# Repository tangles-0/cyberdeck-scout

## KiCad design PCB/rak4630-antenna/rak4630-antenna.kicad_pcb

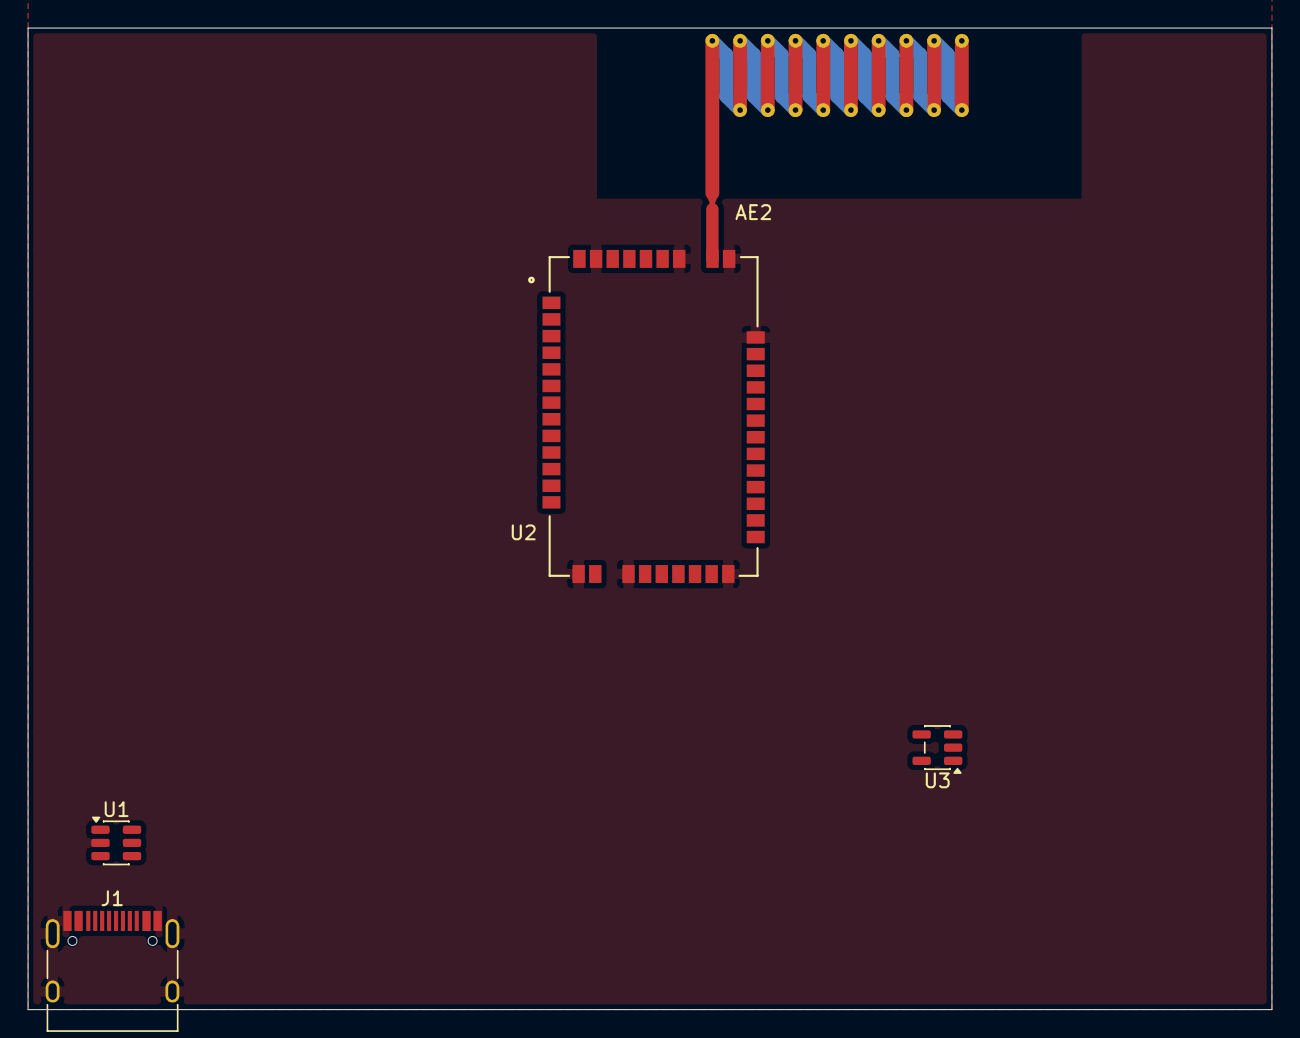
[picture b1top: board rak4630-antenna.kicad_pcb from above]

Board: 2 copper layers, 89.8 x 70.8 mm, 5 parts (0 on the bottom side), 7 nets.

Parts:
AE2: Antenna; Texas_SWRA416_868MHz_915MHz
J1: USB_C_Receptacle_USB2.0_16P; USB_C_Receptacle_HRO_TYPE-C-31-M-12
U1: USBLC6-2SC6; SOT-23-6
U2: RAK4630
U3: AP2112K-3.3; SOT-23-5

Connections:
+VBUS: J1.A4 (VBUS), J1.A9 (VBUS), J1.B4 (VBUS), J1.B9 (VBUS), U1.5 (VBUS), U2.1 (VBUS)
/USBD_N: U1.6 (I/O1), U2.2 (USB-)
/USBD_P: U1.4 (I/O2), U2.3 (USB+)
GND: J1.A1 (GND), J1.A12 (GND), J1.B1 (GND), J1.B12 (GND), J1.S1 (SHIELD), U1.2 (GND), U2.14 (GND1), U2.16 (GND2), U2.22 (GND3), U2.35 (GND4), U2.36 (GND5), U2.38 (GND6), U2.43 (VDD_NRF)
unnamed: AE2.1 (A), U2.37 (RF_LORA)
unnamed: J1.A6 (D+), J1.B6 (D+), U1.3 (I/O2)
unnamed: J1.A7 (D-), J1.B7 (D-), U1.1 (I/O1)

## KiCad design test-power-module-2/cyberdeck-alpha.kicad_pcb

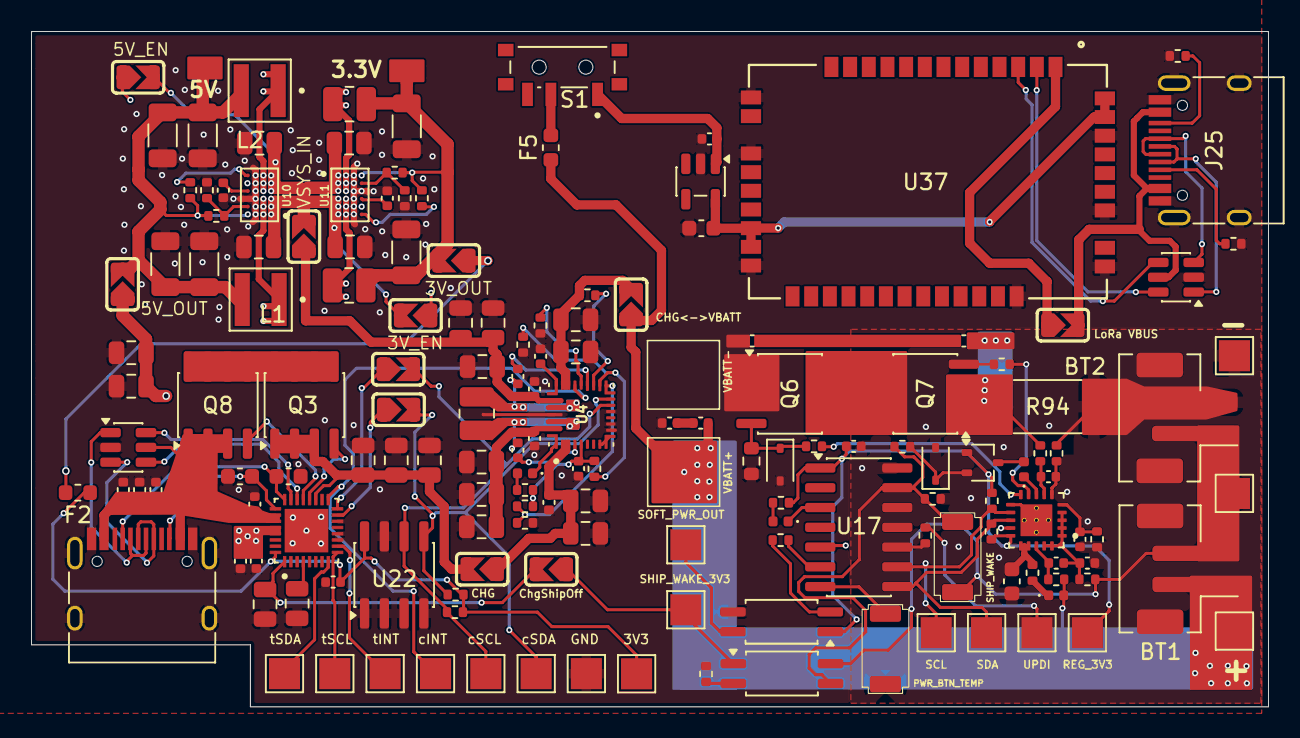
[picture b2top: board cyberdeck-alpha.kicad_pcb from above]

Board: 4 copper layers, 79.5 x 43.4 mm, 158 parts (0 on the bottom side), 103 nets.

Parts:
BT1, BT2: LiCell; JST_PH_B2B-PH-SM4-TB_1x02-1MP_P2.00mm_Vertical
C54, C55, C61, C62, C115, C116: 22uF; C_0805_2012Metric
C56, C57, C58, C59, C64, C65: 47uF; C_1206_3216Metric
C60, C63: 3.3nF; C_0402_1005Metric
C76, C112: 4.7uF; C_0402_1005Metric
C77, C93: 47nF; C_0402_1005Metric
C84, C157: 2.2uF; C_0603_1608Metric
C85, C86, C87: 220nF; C_0402_1005Metric
C88, C89, C90, C91, C92, C100, C101, C106, C107, C113, C114, C119, C120, C123, C139: 100nF; C_0402_1005Metric
C94: 1nF; C_0402_1005Metric
C95, C96, C97, C98, C99, C102, C103, C104, C105, C108, C109, C110, C111, C121, C122: 10uF; C_0805_2012Metric
C117, C118: 330pF; C_0603_1608Metric
C156: 1uF; C_0402_1005Metric
D30, D32: RB161QS-40T18R; D_0402_1005Metric
D31: 1.8V; D_SOD-323
D33: MMSZ5246BS-7-F; D_SOD-323
D35, D36: LED_0402; LED_0402_1005Metric
F2, F5: 500mA; Fuse_0603_1608Metric
J14, J25: USB_C_Receptacle_USB2.0_16P; USB_C_Receptacle_HRO_TYPE-C-31-M-12
K_80, K_86: TS-1088-AR02016; BTN_SMD_4x3mm
L1, L2: 1uH; IND_XFL4020-102MEC
L3, L4, L6: 1uH; L_1008_2520Metric
Q2: CJ2101; SOT-323_SC-70
Q3, Q6, Q7, Q8: SI4174DY-T1-GE3_N-Channel_FET_SOIC-8; SOIC-8_3.9x4.9mm_P1.27mm
R48, R51, R52, R123: 470K; R_0402_1005Metric
R49: 430K; R_0402_1005Metric
R50: 82K; R_0402_1005Metric
R53: 150K; R_0402_1005Metric
R64: 1K; R_0402_1005Metric
R66, R75, R95, R96: 10K; R_0402_1005Metric
R71, R88, R92, R93: 100R; R_0402_1005Metric
R72: 6.04K; R_0402_1005Metric
R73: 127K; R_0402_1005Metric
R74: 100K; R_0402_1005Metric
R85, R86, R128, R129: 5.1K; R_0402_1005Metric
R87: 10M; R_0603_1608Metric
R89, R90, R91: 10R; R_0402_1005Metric
R94: 1m; R_2512_6332Metric
R97: 3.3K; R_0402_1005Metric
R98, R101, R122: 430R; R_0402_1005Metric
R99, R100, R124: 4.7K; R_0402_1005Metric
S1: SSSS811101; SW_SSSS811101
SJ8: 3V_EN; SOLDERJUMPER_ARROW_NOPASTE
SJ9: 5V_EN; SOLDERJUMPER_ARROW_NOPASTE
SJ11: VSYS_IN; SOLDERJUMPER_ARROW_NOPASTE
SJ12: 5V_OUT; SOLDERJUMPER_ARROW_NOPASTE
SJ13: 3V_OUT; SOLDERJUMPER_ARROW_NOPASTE
SJ14, SJ18: SHP_OFF; SOLDERJUMPER_ARROW_NOPASTE
SJ15: PD_PSU; SOLDERJUMPER_ARROW_NOPASTE
SJ16: CHG_SCL; SOLDERJUMPER_ARROW_NOPASTE
SJ17: CHG_SDA; SOLDERJUMPER_ARROW_NOPASTE
SJ19: LoRa VBUS; SOLDERJUMPER_ARROW_NOPASTE
TP1, TP2, TP3, TP4, TP5, TP6, TP7, TP8, TP9, TP10, TP11, TP12, TP13, TP14, TP15, TP16, TP18: TestPoint_Small; TestPoint_Pad_2.0x2.0mm
U4: BQ25792RQMR
U10, U11: TPS62180YZFR; BGA24N50P4X6_310X210X62N
U16: BQ76905RGRR; IC_BQ76905RGRR
U17: ATtiny404-SS; SOIC-14_3.9x8.7mm_P1.27mm
U18: TPS25751SRSMR
U22: AT24CS01-SSHM; SOIC-8_3.9x4.9mm_P1.27mm
U24, U32: AT3H7B-CuH-S; SSOP-4_AT3H7B-CuH-S
U27, U39: USBLC6-2SC6; SOT-23-6
U37: RAK4630
U38: TPS70933DBVR; SOT-23-5

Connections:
+3.3V_LORA: C157.2, U37.20 (VBAT_SX), U37.21 (VBAT_IO_SX), U37.43 (VDD_NRF), U37.44 (VBAT_NRF), U38.5 (VOUT)
+3.3V_MAIN: F2.2, SJ13.1
+5V_MAIN: C119.1, C120.1, C121.1, C122.1, SJ12.1, U18.28 (PP5V), U18.29 (PP5V)
+VBATT: BT1.1 (+), C92.1, C95.1, C96.2, D30.2 (A), F5.1, R71.2, R89.2, SJ18.1, SJ18.2, TP1.1 (1_1), U4.22 (BAT), U4.23 (BAT)
+VBUS: C106.1, C112.1, C113.1, C114.1, J14.A4 (VBUS), J14.A9 (VBUS), J14.B4 (VBUS), J14.B9 (VBUS), Q8.1 (S), Q8.2 (S), Q8.3 (S), U18.26 (VBUS), U18.27 (VBUS), U27.5 (VBUS)
+VCHG: C101.1, C102.1, C103.2, SJ15.1, U4.2 (VBUS), U4.3 (VBUS)
+VSYS: C107.1, C108.2, C109.2, C110.2, SJ11.1, U4.25 (SYS)
/3V3_MAIN: C64.2, C65.2, L3.2, L4.2, R51.2, R52.2, SJ13.2, U11.A4 (VO)
/5V_MAIN: C56.2, C57.2, C58.2, C59.2, L1.2, L2.2, R48.2, R49.2, SJ12.2, U10.A4 (VO)
/+VCHG_OUT: C111.1, C115.1, C116.1, Q3.1 (S), Q3.2 (S), Q3.3 (S), SJ15.2, U18.19 (VSYS)
/BQ_ALERT: U16.14 (ALERT), U17.5 (PA7)
/BQ_BATT+: C85.2, R89.1, U16.18 (VC5)
/BQ_BATT-: C87.2, R91.1, U16.5 (VC0)
/BQ_CELL1: C85.1, C86.2, R90.1, U16.1 (VC3A), U16.2 (VC3B), U16.3 (VC2), U16.4 (VC1), U16.19 (VC4A), U16.20 (VC4B)
/BQ_CHG: R86.2, U16.10 (CHG)
/BQ_DSG: R85.2, U16.9 (DSG)
/BQ_REGOUT_3V3: C139.1, Q2.1 (G), R66.1, R95.1, R98.2, TP13.1 (1_1), U16.15 (REGOUT), U17.1 (VCC), U32.1
/BQ_REGSRC: C84.2, R88.1, U16.16 (REGSRC), U16.17 (BAT)
/BQ_SCL: R66.2, TP15.1 (1_1), U16.12 (SCL), U17.9 (PB0)
/BQ_SDA: R95.2, TP14.1 (1_1), U16.13 (SDA), U17.8 (PB1)
/BQ_TS: D32.1 (K), U16.8 (TS)
/CELL1: BT1.2 (-), BT2.1 (+), K_86.2, R90.2, TP2.1 (1_1), U24.4
/CHG_INT: TP12.1 (1_1), U4.21 (~INT), U18.17 (I2Cc_IRQ)
/CHG_SCL: R100.1, SJ16.2, TP10.1 (1_1), U4.14 (SCL), U22.6 (SCL)
/CHG_SDA: R124.1, SJ17.2, TP11.1 (1_1), U4.15 (SDA), U22.5 (SDA)
/CHG_USBD_N: U18.23 (GPIO5/USB_N/MD2), U27.6 (I/O1)
/CHG_USBD_P: U18.22 (GPIO5/USB_P/MD1), U27.4 (I/O2)
/CM5_PWR_BTN: TP16.1 (1_1), U32.4
/DSCH_PATH: C89.2, Q7.1 (S), Q7.2 (S), Q7.3 (S), R93.2, R94.1
/GATE_VBUS: Q8.4 (G), U18.21 (GATE_VBUS)
/GATE_VCHG: Q3.4 (G), U18.20 (GATE_VSYS)
/HUB2_DS_1_D+: U37.2 (USB-), U39.6 (I/O1)
/HUB2_DS_1_D-: U37.3 (USB+), U39.4 (I/O2)
/IRQt: TP6.1 (1_1), U18.10 (I2Ct_IRQ)
/LORA_VBUS: J25.A4 (VBUS), J25.A9 (VBUS), J25.B4 (VBUS), J25.B9 (VBUS), SJ19.2, U39.5 (VBUS)
/PD_3V3: C123.1, F2.1, R100.2, R124.2, TP9.1 (1_1), U18.32 (VIN_3V3), U22.8 (VCC)
/PD_CC1: C117.2, J14.A5 (CC1), U18.24 (CC1)
/PD_CC2: C118.2, J14.B5 (CC2), U18.25 (CC2)
/PMID: C97.1, C98.2, C99.2, C100.1, U4.29 (PMID)
/PWR_BTN: K_80.1, U17.7 (PB2)
/PWR_OK_3V3: R51.1, U11.F4 (PG)
/PWR_OK_5V: R48.1, U10.F4 (PG)
/REGN: C76.2, R73.2, R75.1, R97.2, U4.5 (REGN)
/SCLc: SJ16.1, U18.16 (I2Cc_SCL)
/SCLt: TP8.1 (1_1), U18.9 (I2Ct_SCL)
/SDAc: SJ17.1, U18.15 (I2Cc_SDA)
/SDAt: TP7.1 (1_1), U18.8 (I2Ct_SDA)
/SHIP_MODE_WAKE_BTN: K_86.1, R64.1, R123.2, U17.13 (PA3), U24.3
/SHIP_WAKE_3V3: SJ14.1, TP18.1 (1_1), U24.1
/SOFT_PWR_OUT: R101.2, U17.6 (PB3)
/TINY202_UPDI: R99.2, TP4.1 (1_1)
/TPS_LDO_3V3: C104.1, SJ14.2, U18.1 (LDO_3V3)
/VBATT_LORA: C156.1, S1.1, U38.1 (VIN)
/VSYS_IN: C54.2, C55.2, C61.2, C62.2, SJ8.2, SJ9.2, SJ11.2, U10.A1 (VIN1), U10.B1 (VIN1), U10.C1 (VIN1), U10.D1 (VIN2), U10.E1 (VIN2), U10.F1 (VIN2), U11.A1 (VIN1), U11.B1 (VIN1), U11.C1 (VIN1), U11.D1 (VIN2), U11.E1 (VIN2), U11.F1 (VIN2)
BATT_GND: BT2.2 (-), C84.1, C86.1, C87.1, C139.2, D31.2 (A), K_80.2, R91.2, R92.1, R94.2, R123.1, TP5.1 (1_1), U16.11 (VSS), U16.21 (EXP), U17.14 (GND)
GND: C54.1, C55.1, C56.1, C57.1, C58.1, C59.1, C60.1, C61.1, C62.1, C63.1, C64.1, C65.1, C76.1, C90.1, C91.2, C94.2, C95.2, C96.1, C97.2, C98.1, C99.1, C100.2, C101.2, C102.2, C103.1, C104.2, C105.2, C106.2, C107.2, C108.1, C109.1, C110.1, C111.2, C112.2, C113.2, C114.2, C115.2, C116.2, C117.1, C118.1, C119.2, C120.2, C121.2, C122.2, C123.2, C156.2, C157.1, D33.2 (A), J14.A1 (GND), J14.A12 (GND), J14.B1 (GND), J14.B12 (GND), J14.S1 (SHIELD), J25.A1 (GND), J25.A12 (GND), J25.B1 (GND), J25.B12 (GND), J25.S1 (SHIELD), Q6.1 (S), Q6.2 (S), Q6.3 (S), R50.1, R53.1, R72.1, R74.1, R87.1, R96.2, R122.1, R128.1, R129.1, TP3.1 (1_1), U4.10 (ACDRV2), U4.11 (ACDRV1), U4.13 (~CE), U4.27 (GND), U10.A3 (PGND), U10.B3 (PGND), U10.C3 (PGND), U10.C4 (AGND), U10.D3 (PGND), U10.E3 (PGND), U10.F3 (PGND), U11.A3 (PGND), U11.B3 (PGND), U11.C3 (PGND), U11.C4 (AGND), U11.D3 (PGND), U11.E3 (PGND), U11.F3 (PGND), U18.11 (GND), U18.12 (GND), U18.14 (GND), U18.33 (GND), U22.1 (A0), U22.2 (A1), U22.3 (A2), U22.4 (GND), U22.7 (WP), U27.2 (GND), U32.3, U37.14 (GND1), U37.16 (GND2), U37.22 (GND3), U37.35 (GND4), U37.36 (GND5), U37.38 (GND6), U37.42 (GND7), U38.2 (GND), U39.2 (GND)
unnamed: C89.1, C90.2
unnamed: C91.1, C92.2
unnamed: D30.1 (K), R88.2
unnamed: D31.1 (K), Q2.2 (S), R64.2
unnamed: D32.2 (A), Q2.3 (D)
unnamed: D33.1 (K), Q6.4 (G), R86.1, R87.2
unnamed: D35.2 (A), R97.1
unnamed: D35.1 (K), U4.1 (STAT)
unnamed: D36.2 (A), R98.1
unnamed: D36.1 (K), U17.3 (PA5)
unnamed: F5.2, S1.2
unnamed: J14.A6 (D+), J14.B6 (D+), U27.3 (I/O2)
unnamed: J14.A7 (D-), J14.B7 (D-), U27.1 (I/O1)
unnamed: J25.A5 (CC1), R129.2
unnamed: J25.B5 (CC2), R128.2
unnamed: J25.A6 (D+), J25.B6 (D+), U39.3 (I/O2)
unnamed: J25.A7 (D-), J25.B7 (D-), U39.1 (I/O1)
unnamed: L1.1, U10.A2 (SW1), U10.B2 (SW1), U10.C2 (SW1)
unnamed: L2.1, U10.D2 (SW2), U10.E2 (SW2), U10.F2 (SW2)
unnamed: L3.1, U11.A2 (SW1), U11.B2 (SW1), U11.C2 (SW1)
unnamed: L4.1, U11.D2 (SW2), U11.E2 (SW2), U11.F2 (SW2)
unnamed: Q3.5 (D), Q3.6 (D), Q3.7 (D), Q3.8 (D), Q8.5 (D), Q8.6 (D), Q8.7 (D), Q8.8 (D)
unnamed: Q6.5 (D), Q6.6 (D), Q6.7 (D), Q6.8 (D), Q7.5 (D), Q7.6 (D), Q7.7 (D), Q7.8 (D)
unnamed: Q7.4 (G), R85.1
unnamed: R101.1, U32.2
unnamed: R122.2, U24.2
unnamed: R71.1, U4.18 (BATP)
unnamed: C77.1, U4.4 (BTST1)
unnamed: C93.1, U4.19 (BTST2)
unnamed: R73.1, R74.2, U4.17 (ILIM_HIZ)
unnamed: R72.2, U4.20 (PROG)
unnamed: C94.1, U4.24 (SDRV)
unnamed: C77.2, L6.1, U4.28 (SW1)
unnamed: C93.2, L6.2, U4.26 (SW2)
unnamed: R75.2, R96.1, U4.16 (TS)
unnamed: U4.8 (VAC2), U4.9 (VAC1)
unnamed: SJ9.1, U10.E4 (EN)
unnamed: R49.1, R50.2, U10.B4 (FB)
unnamed: C60.2, U10.D4 (SS/TR)
unnamed: SJ8.1, U11.E4 (EN)
unnamed: R52.1, R53.2, U11.B4 (FB)
unnamed: C63.2, U11.D4 (SS/TR)
unnamed: C88.1, R93.1, U16.7 (SRN)
unnamed: C88.2, R92.2, U16.6 (SRP)
unnamed: R99.1, U17.10 (~RESET/PA0)
unnamed: C105.1, U18.4 (LDO_1V5)
unnamed: SJ19.1, U37.1 (VBUS)

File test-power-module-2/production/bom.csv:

Designator,Footprint,Quantity,Value,LCSC Part #
"BT1, BT2",JST_PH_B2B-PH-SM4-TB_1x02-1MP_P2.00mm_Vertical,2,LiCell,C7433663 
"C100, C101, C106, C107, C113, C114, C119, C120, C123, C139, C88, C89, C90, C91, C92",0402,15,100nF,C1525 
"C102, C103, C104, C105, C108, C109, C110, C111, C121, C122, C95, C96, C97, C98, C99",0805,15,10uF,C15850 
"C112, C76",0402,2,4.7uF,C23733
"C115, C116, C54, C55, C61, C62",0805,6,22uF,C6119899 
"C117, C118",0603,2,330pF,C1664
C156,0402,1,1uF,C52923
"C157, C84",0603,2,2.2uF,C23630
"C56, C57, C58, C59, C64, C65",1206,6,47uF,C5448950
"C60, C63",0402,2,3.3nF,C1536
"C77, C93",0402,2,47nF,C1538
"C85, C86, C87",0402,3,220nF,C16772
C94,0402,1,1nF,C1523
"D30, D32",0402,2,RB161QS-40T18R,C2837790 
D31,D_SOD-323,1,1.8V,C779376
D33,D_SOD-323,1,MMSZ5246BS-7-F,C151819 
"D35, D36",0402,2,LED_0402,C41366936 
"F2, F5",0603,2,500mA,C210357
"J14, J25",USB_C_Receptacle_HRO_TYPE-C-31-M-12,2,USB_C_Receptacle_USB2.0_16P,C165948
"K_80, K_86",BTN_SMD_4x3mm,2,TS-1088-AR02016,C720477 
L1,IND_XFL4020-102MEC,1,1uH,C5355380 
L2,IND_XFL4020-102MEC,1,1uH,C5355380
"L3, L4, L6",1008,3,1uH,C882955 
Q2,SOT-323_SC-70,1,CJ2101,C52641 
"Q3, Q6, Q7, Q8",SOIC-8_3.9x4.9mm_P1.27mm,4,SI4174DY-T1-GE3_N-Channel_FET_SOIC-8,C144929
"R100, R124, R99",0402,3,4.7K,C25900
"R101, R122, R98",0402,3,430R,C36356
"R123, R48, R51, R52",0402,4,470K,C177264
"R128, R129, R85, R86",0402,4,5.1K,C25905 
R49,0402,1,430K,C131588
R50,0402,1,82K,C4142
R53,0402,1,150K,C25755
R64,0402,1,1K,C11702 
"R66, R75, R95, R96",0402,4,10K,C25744
"R71, R88, R92, R93",0402,4,100R,C25076
R72,0402,1,6.04K,C25913
R73,0402,1,127K,C5126094
R74,0402,1,100K,C25741
R87,0603,1,10M,C7250
"R89, R90, R91",0402,3,10R,C25077
R94,2512,1,1m,C19270875
R97,0402,1,3.3K,C25890
S1,SW_SSSS811101,1,SSSS811101,C109335
"U10, U11",BGA24N50P4X6_310X210X62N,2,TPS62180YZFR,C2071394 
U16,IC_BQ76905RGRR,1,BQ76905RGRR,C22394458 
U17,SOIC-14_3.9x8.7mm_P1.27mm,1,ATtiny404-SS,
U18,TPS25751SRSMR,1,TPS25751SRSMR,C22460852
U22,SOIC-8_3.9x4.9mm_P1.27mm,1,AT24CS01-SSHM,C12371
"U24, U32",SSOP-4_AT3H7B-CuH-S,2,AT3H7B-CuH-S,C20612660
"U27, U39",SOT-23-6,2,USBLC6-2SC6,C2827654
U37,RAK4630,1,RAK4630,C33033533
U38,SOT-23-5,1,TPS70933DBVR,C89347
U4,BQ25792RQMR,1,BQ25792RQMR,C2862876
